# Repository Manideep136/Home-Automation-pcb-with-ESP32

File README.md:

# Home-Automation-pcb-with-ESP32

A custom PCB-based home automation system designed around the ESP32 microcontroller. The project is designed to control high-current AC loads using relay switching while providing a compact and organized PCB for the control electronics.

## Project Overview

This project focuses on designing a dedicated home automation PCB using an **ESP32** as the main controller.

The PCB is designed to interface with a high-current relay for controlling electrical loads. The design was created using **KiCad**, including the schematic, PCB layout, custom footprint, and 3D model integration.

The main goal of this project is to develop a practical and customizable hardware platform for ESP32-based home automation applications.

## Features

- ESP32-based control system
- High-current relay switching
- Designed for loads up to **30A** (relay/load rating dependent)
- Custom PCB designed in KiCad
- Screw terminal connections for external wiring
- Dedicated relay footprint
- Compact PCB layout
- Custom relay footprint and 3D model
- Designed with PCB routing and clearance considerations
- Suitable as a base platform for IoT and home automation projects

## Hardware

### Main Components

| Component | Description |
|---|---|
| ESP32 | Main microcontroller |
| 30A Relay | High-current load switching |
| Power Supply | Provides required DC power |
| Screw Terminals | Load and power connections |
| PCB | Custom KiCad-designed board |

### Relay

The PCB uses a **PR13-5V-450-1C 5V relay** footprint.

The relay footprint was integrated into KiCad using a custom `.kicad_mod` footprint.

> **Important:** The actual safe switching current depends on the relay's datasheet, PCB design, connector rating, wire size, enclosure, and the type of load. Do not assume that every 30A load is safe simply because the relay is labeled 30A.

## PCB Design

The PCB was designed using **KiCad 10**.
KiCad Files
Schematic

The schematic contains the electrical connections between the ESP32, relay, power connections, and other components.

Home automation with ESP32.kicad_sch
PCB

The PCB layout contains the physical board design, component placement, copper tracks, board outline, and routing.

Home automation with ESP32.kicad_pcb
Project

The main KiCad project file is:

Home automation with ESP32.kicad_pro
Custom Footprint

A custom footprint was added for the relay:

PR13-5V-450-1C.pretty/
└── RELAY_PR13-5V-450-1C.kicad_mod

A STEP model is also included for 3D visualization:

PR13-5V-450-1C.step
Working Principle

The basic operating concept is:

          ESP32
            │
            │ Control Signal
            ▼
       Relay Driver
            │
            ▼
       5V Relay Coil
            │
            ▼
     Relay Contacts
            │
            ▼
       AC Load

The ESP32 provides the control signal to operate the relay. The relay electrically switches the connected load.

Additional sensors and IoT functionality can be integrated into the ESP32 firmware depending on the application.

PCB Design Considerations

Because the PCB is intended for high-current switching, special attention should be given to:

PCB trace width
Copper thickness
Clearance between high-voltage and low-voltage sections
Creepage distance
Connector current rating
Relay contact rating
Wire gauge
Fuse/protection
Thermal considerations
Enclosure and insulation

The PCB should be reviewed against the applicable electrical safety requirements before being connected to mains power.

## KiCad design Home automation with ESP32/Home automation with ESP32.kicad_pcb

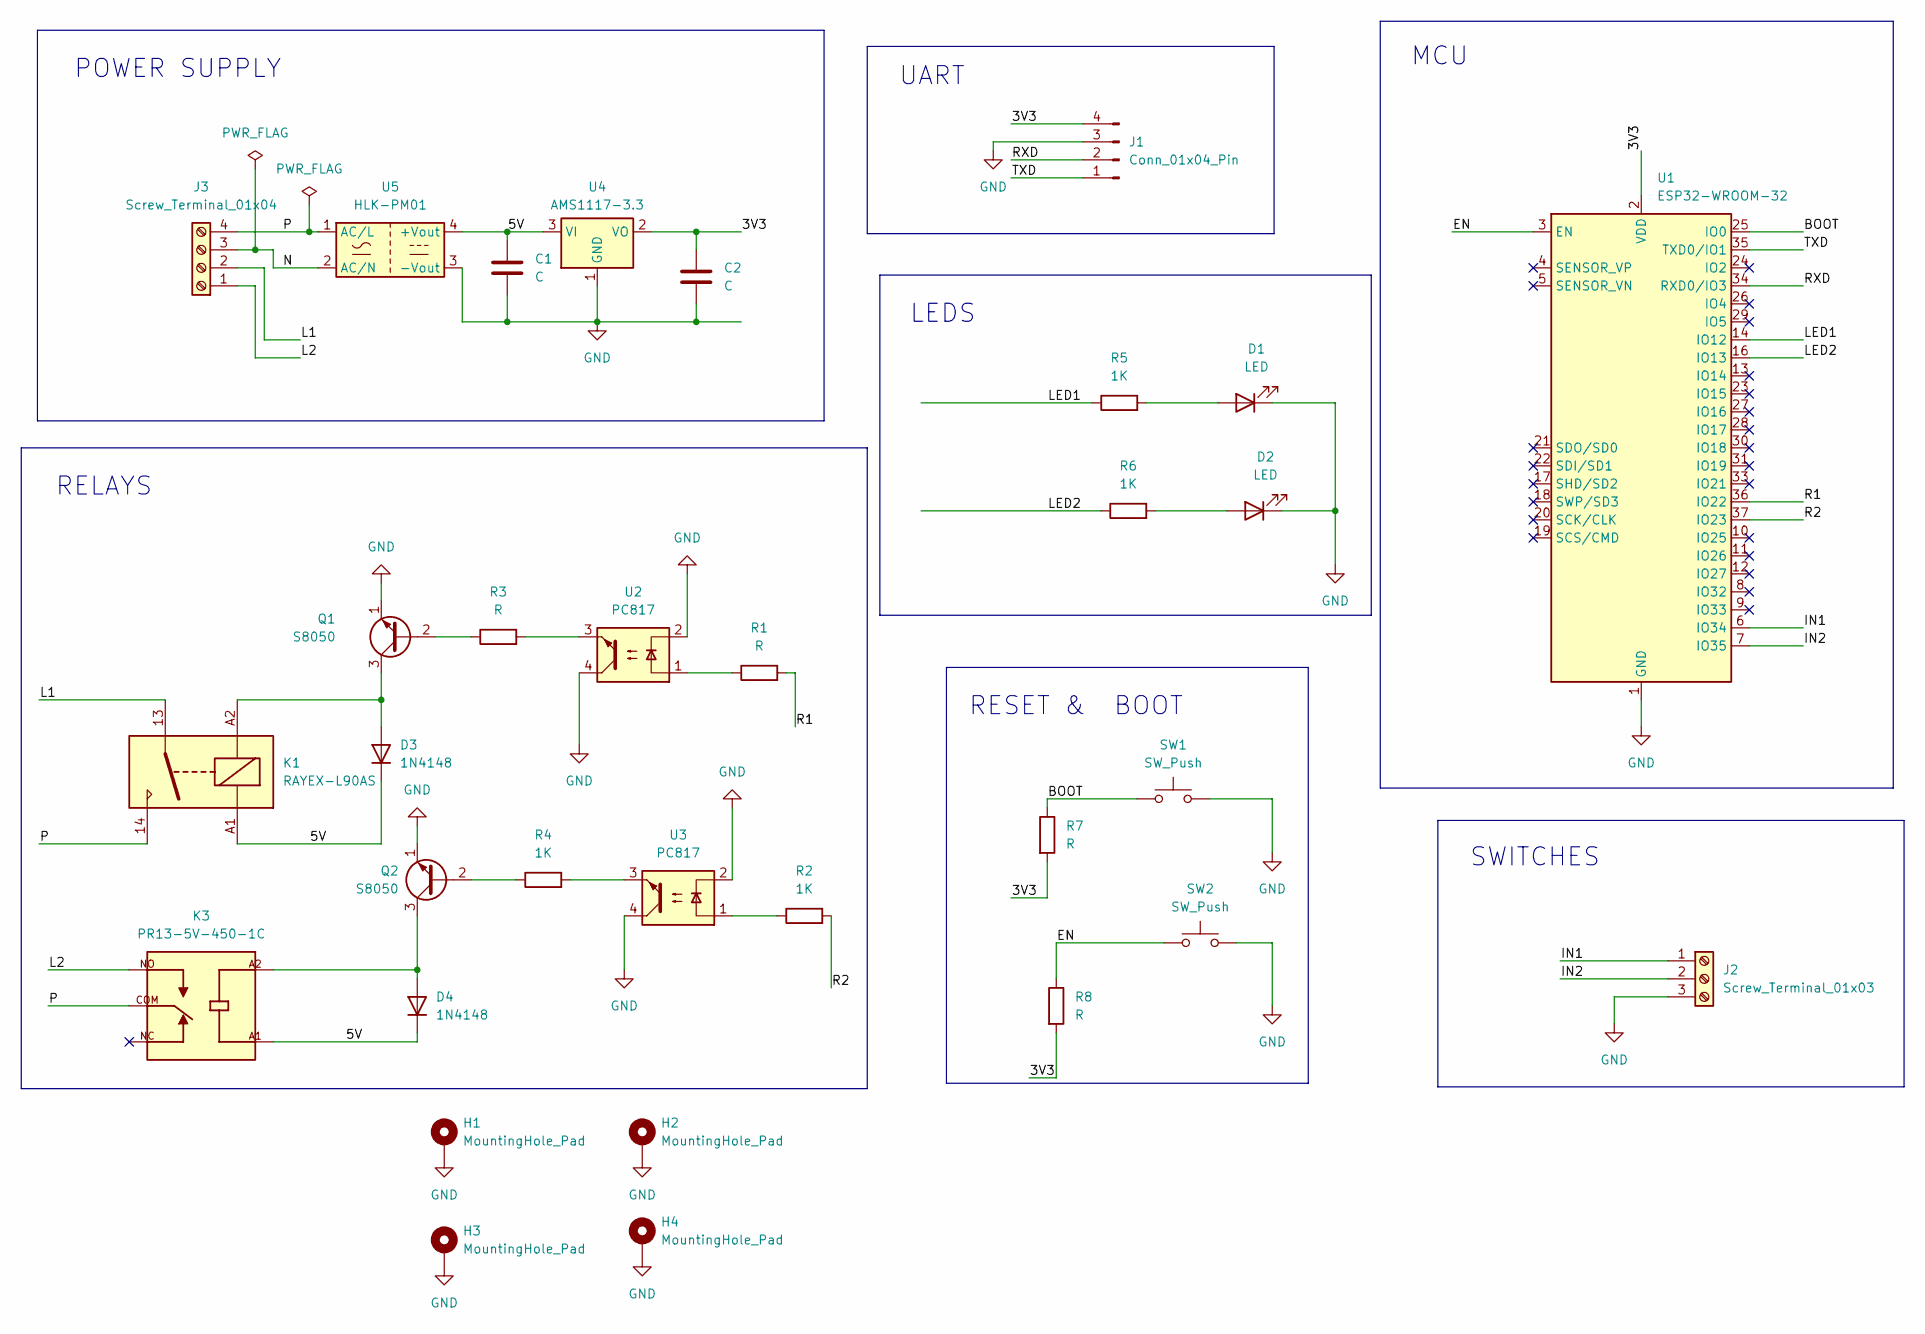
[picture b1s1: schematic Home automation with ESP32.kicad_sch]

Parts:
C1, C2: C; C_0805_2012Metric
D1, D2: LED; LED_0805_2012Metric
D3, D4: 1N4148; D_DO-35_SOD27_P7.62mm_Horizontal
H1, H2, H3, H4: MountingHole_Pad; MountingHole_2.7mm_M2.5_Pad_Via
J1: Conn_01x04_Pin; PinHeader_1x04_P2.54mm_Vertical
J2: Screw_Terminal_01x03; TerminalBlock_Phoenix_MKDS-1,5-3_1x03_P5.00mm_Horizontal
J3: Screw_Terminal_01x04; TerminalBlock_Phoenix_MKDS-1,5-4_1x04_P5.00mm_Horizontal
K1: RAYEX-L90AS; Relay_SPST_RAYEX-L90AS
K3: PR13-5V-450-1C; RELAY_PR13-5V-450-1C; PARTREV 1.0
Q1, Q2: S8050; TO-92_Inline
R1, R3, R7, R8: R; R_0805_2012Metric
R2, R4, R5, R6: 1K; R_0805_2012Metric
SW1, SW2: SW_Push; SW_PUSH_6mm
U1: ESP32-WROOM-32
U2, U3: PC817; DIP-4_W7.62mm
U4: AMS1117-3.3; SOT-223-3_TabPin2
U5: HLK-PM01; Converter_ACDC_Hi-Link_HLK-PMxx

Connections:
/3V3: C2.1, J1.4, R7.2, R8.2, U1.2 (VDD), U4.2 (VO)
/5V: C1.1, D3.1 (K), D4.1 (K), K1.A1, K3.A1, U4.3 (VI), U5.4 (+Vout)
/BOOT: R7.1, SW1.1, U1.25 (IO0)
/EN: R8.1, SW2.1, U1.3 (EN)
/IN1: J2.1, U1.6 (IO34)
/IN2: J2.2, U1.7 (IO35)
/L1: J3.2, K1.13
/L2: J3.1, K3.NO
/LED1: R5.1, U1.14 (IO12)
/LED2: R6.1, U1.16 (IO13)
/N: J3.3, U5.2 (AC/N)
/P: J3.4, K1.14, K3.COM, U5.1 (AC/L)
/R1: R1.2, U1.36 (IO22)
/R2: R2.2, U1.37 (IO23)
/RXD: J1.2, U1.34 (RXD0/IO3)
/TXD: J1.1, U1.35 (TXD0/IO1)
GND: C1.2, C2.2, D1.1 (K), D2.1 (K), H1.1 (1_1), H2.1 (1_1), H3.1 (1_1), H4.1 (1_1), J1.3, J2.3, Q1.1 (E), Q2.1 (E), SW1.2, SW2.2, U1.1 (GND), U1.15 (GND), U1.38 (GND), U1.39 (GND), U2.2, U2.4, U3.2, U3.4, U4.1 (GND), U5.3 (-Vout)
unnamed: D1.2 (A), R5.2
unnamed: D2.2 (A), R6.2
unnamed: D3.2 (A), K1.A2, Q1.3 (C)
unnamed: D4.2 (A), K3.A2, Q2.3 (C)
unnamed: Q1.2 (B), R3.1
unnamed: Q2.2 (B), R4.1
unnamed: R1.1, U2.1
unnamed: R2.1, U3.1
unnamed: R3.2, U2.3
unnamed: R4.2, U3.3

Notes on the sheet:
LEDS
POWER SUPPLY
UART
SWITCHES
RESET & BOOT
MCU
RELAYS

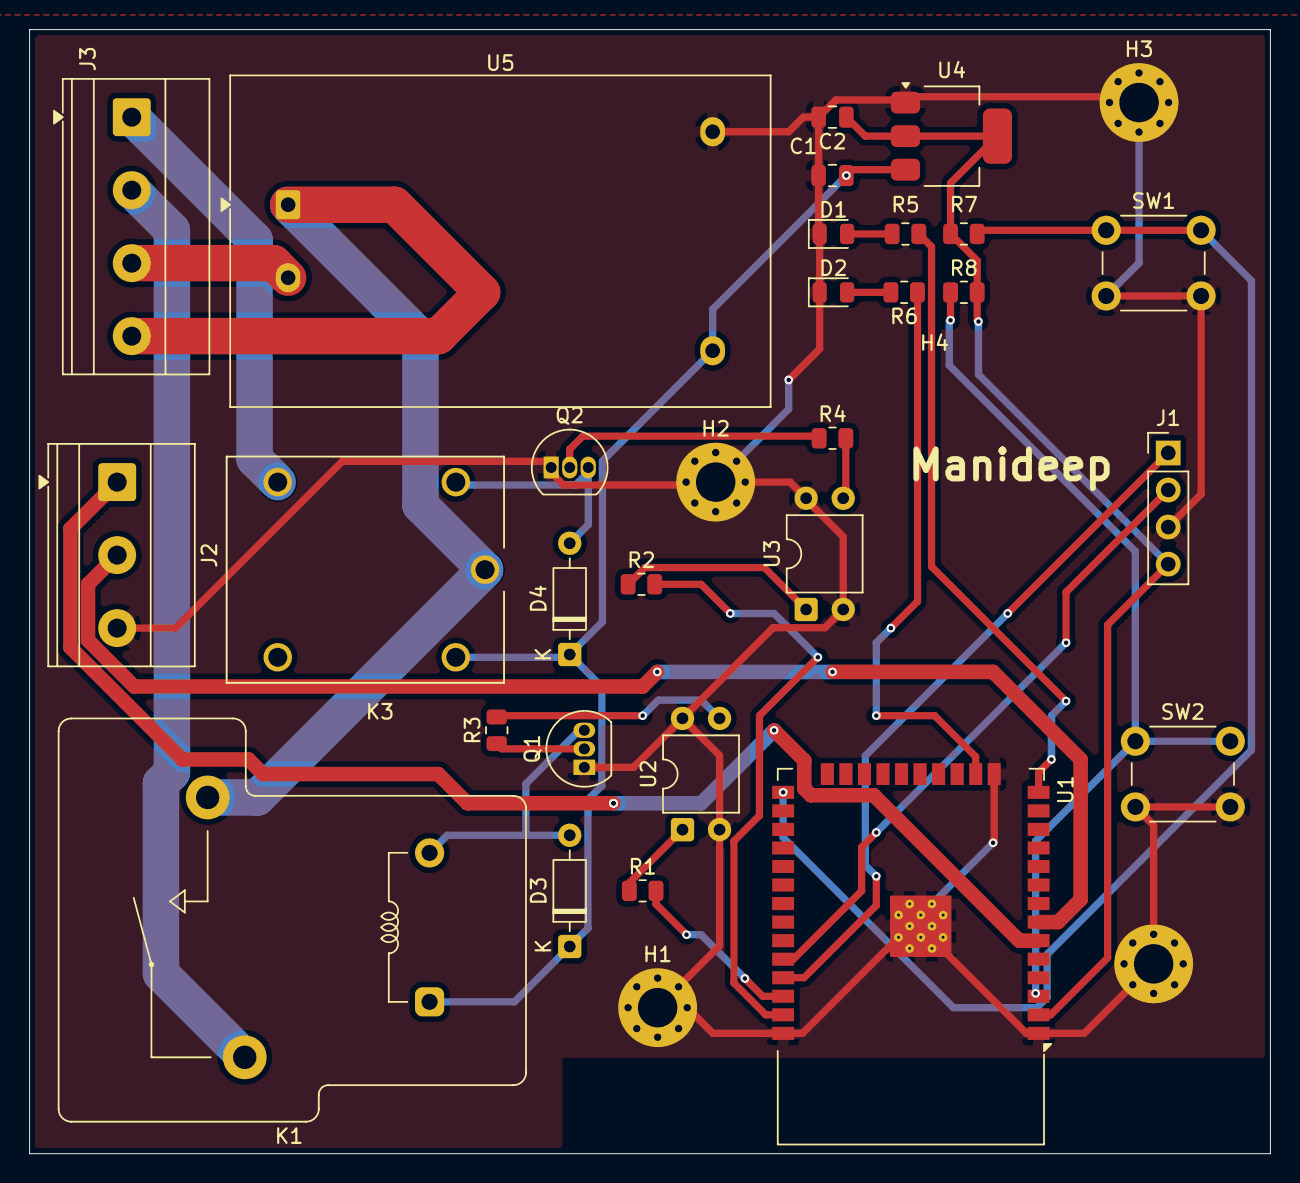
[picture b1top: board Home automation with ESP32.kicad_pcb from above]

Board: 2 copper layers, 85.0 x 77.0 mm, 32 parts (0 on the bottom side), 27 nets.
